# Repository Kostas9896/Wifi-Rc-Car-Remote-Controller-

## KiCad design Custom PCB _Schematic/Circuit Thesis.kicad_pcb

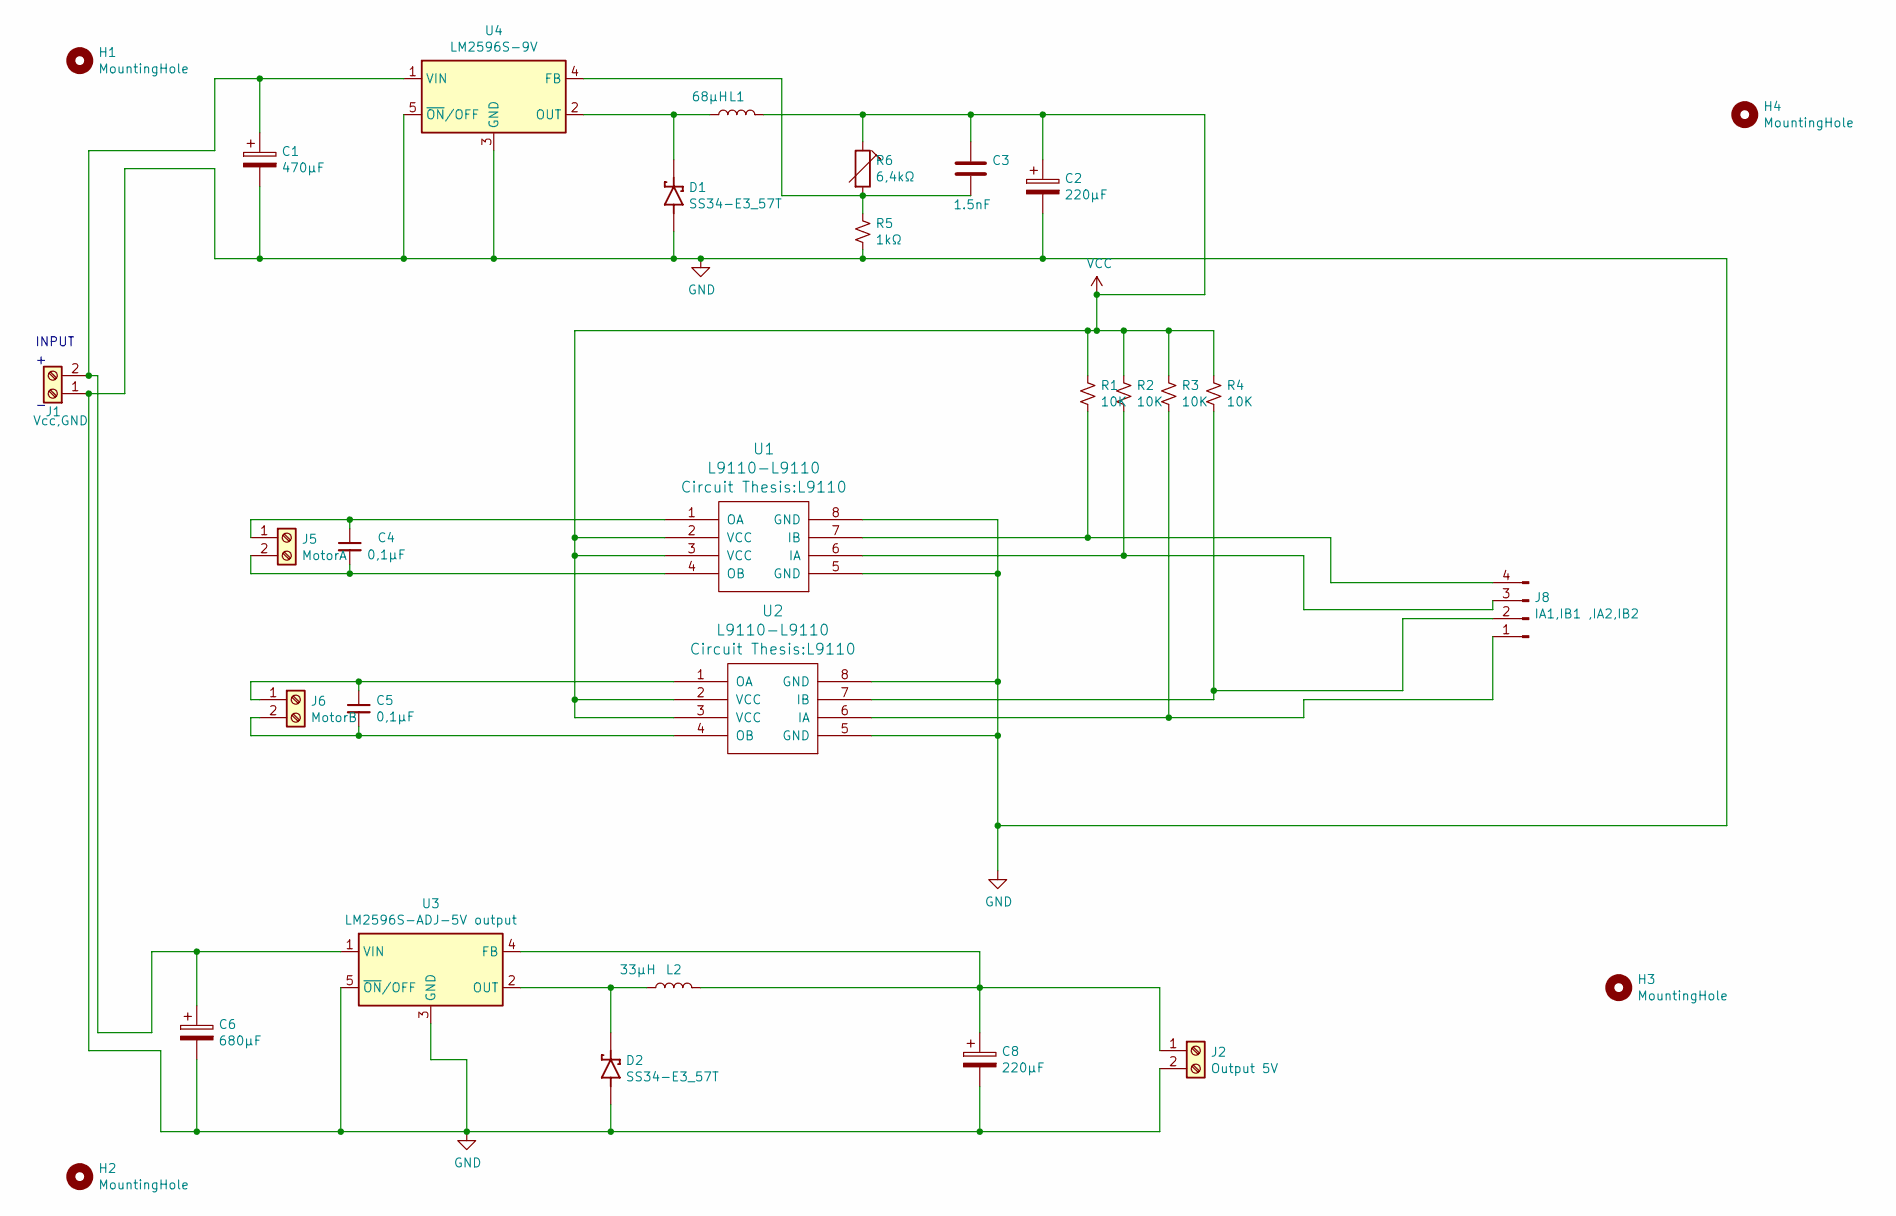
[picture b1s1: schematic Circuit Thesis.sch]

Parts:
C1: 470μF; CP_Elec_16x17.5
C2, C8: 220μF; CP_Elec_10x10.5
C3: 1.5nF; CP_EIA-1608-08_AVX-J
C4, C5: 0,1μF; CP_EIA-3216-10_Kemet-I
C6: 680μF; CP_Elec_16x17.5
D1, D2: SS34-E3_57T; DIOM7959X262N
H1, H2, H3, H4: MountingHole; MountingHole_2.1mm
J1: Vcc,GND; TerminalBlock_bornier-2_P5.08mm
J2: Output 5V; TerminalBlock_bornier-2_P5.08mm
J5: MotorA; TerminalBlock_bornier-2_P5.08mm
J6: MotorB; TerminalBlock_bornier-2_P5.08mm
J8: IA1,IB1 ,IA2,IB2; PinHeader_1x04_P2.00mm_Vertical
L1: 68μH; L_7.3x7.3_H4.5
L2: 33μH; L_7.3x7.3_H4.5
R1, R2, R3, R4: 10K; R_0805_2012Metric
R5: 1kΩ; R_0805_2012Metric
R6: 6,4kΩ; Potentiometer_Bourns_3269W_Vertical
U1, U2: L9110-L9110; L9110
U3: LM2596S-ADJ-5V output; TO-263-5_TabPin3
U4: LM2596S-9V; TO-263-5_TabPin3

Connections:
GND: C1.2, C2.2, C6.2, C8.2, D1.A, D2.A, J1.1, J2.2, R5.2, U1.5 (GND), U1.8 (GND), U2.5 (GND), U2.8 (GND), U3.3 (GND), U3.5 (~ON~/OFF), U4.3 (GND), U4.5 (~ON~/OFF)
unnamed: C1.1, C6.1, J1.2, U3.1 (VIN), U4.1 (VIN)
unnamed: C3.2, R5.1, R6.2, U4.4 (FB)
unnamed: C4.1, J5.1, U1.1 (OA)
unnamed: C4.2, J5.2, U1.4 (OB)
unnamed: C5.1, J6.1, U2.1 (OA)
unnamed: C5.2, J6.2, U2.4 (OB)
unnamed: C8.1, J2.1, L2.2, U3.4 (FB)
unnamed: D1.C, L1.1, U4.2 (OUT)
unnamed: D2.C, L2.1, U3.2 (OUT)
unnamed: J8.1, R3.2, U2.6 (IA)
unnamed: J8.2, R4.2, U2.7 (IB)
unnamed: J8.3, R2.2, U1.6 (IA)
unnamed: J8.4, R1.2, U1.7 (IB)
VCC: C2.1, C3.1, L1.2, R1.1, R2.1, R3.1, R4.1, R6.1, U1.2 (VCC), U1.3 (VCC), U2.2 (VCC), U2.3 (VCC)

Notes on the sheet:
INPUT

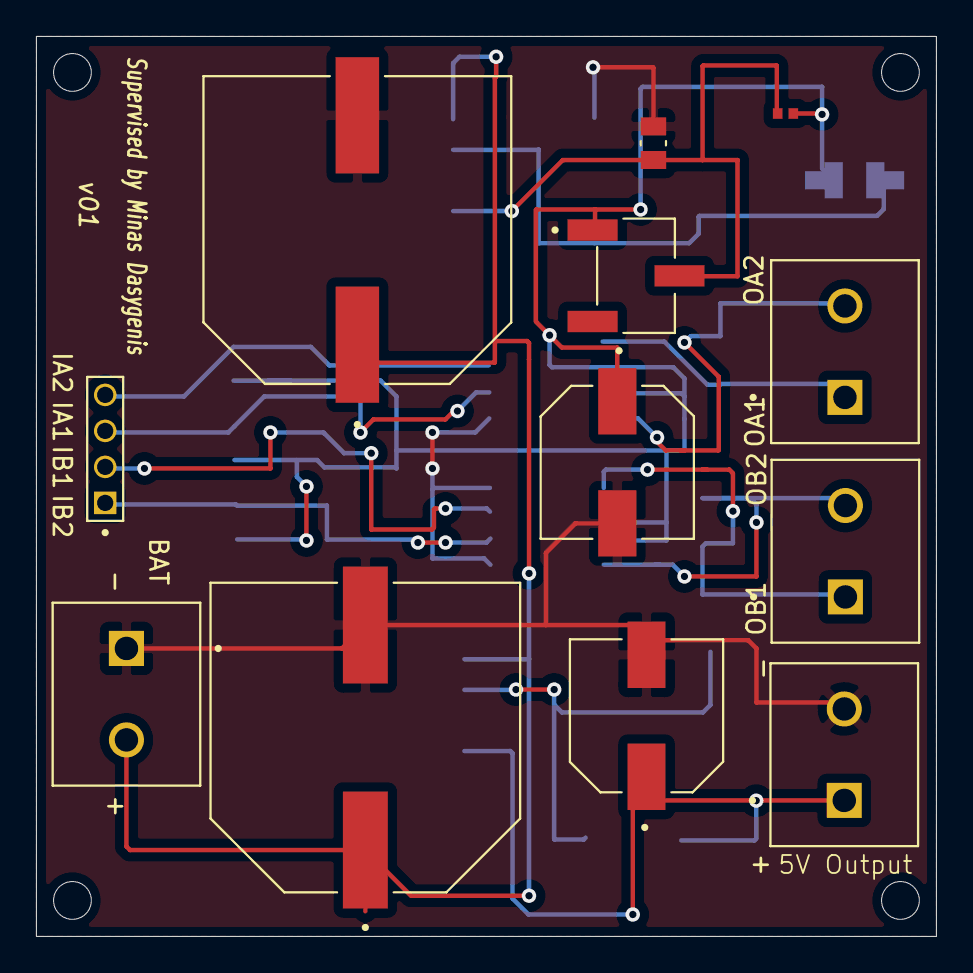
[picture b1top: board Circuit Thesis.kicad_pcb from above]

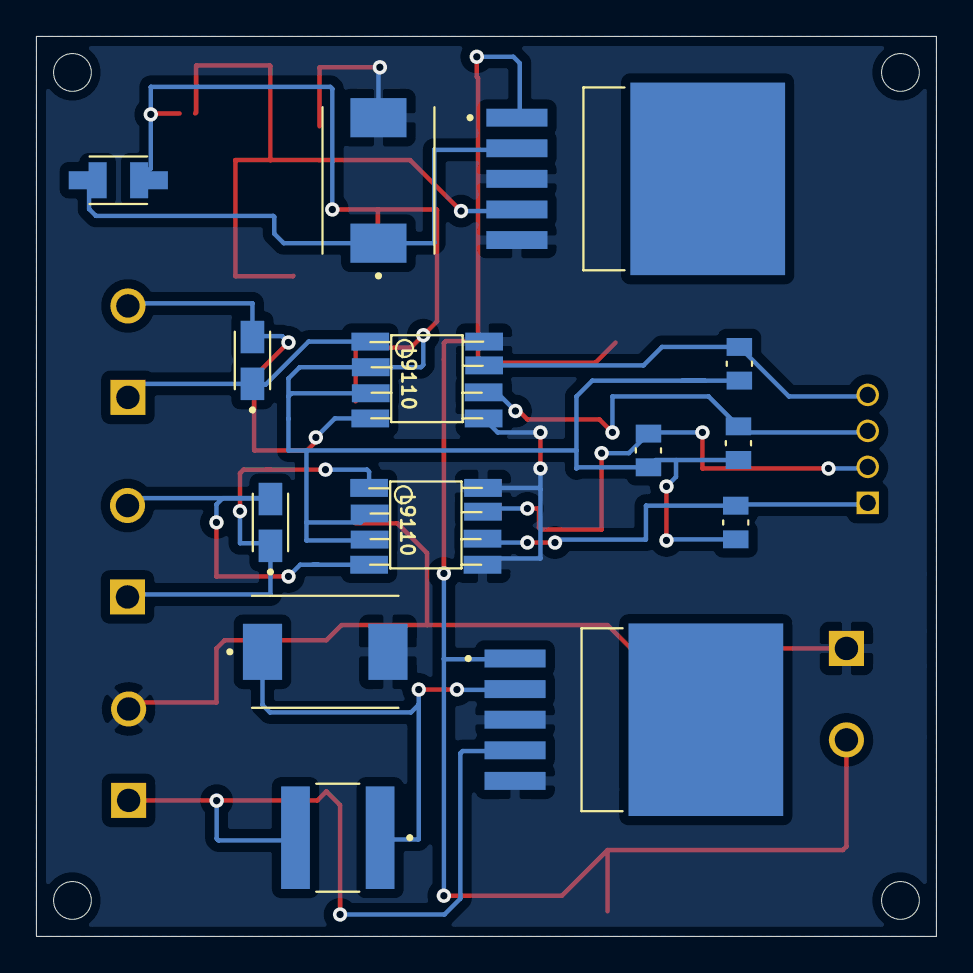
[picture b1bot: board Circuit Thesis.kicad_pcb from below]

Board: 2 copper layers, 50.0 x 50.0 mm, 30 parts (14 on the bottom side), 15 nets.

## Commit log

2021-09-03 second
2021-09-03 Third Commit
2021-09-03 Android app
2021-09-04 test
2021-09-04 pameeee
